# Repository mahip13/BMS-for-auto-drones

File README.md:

This directory contains schematics and simulationsfor the BMS for autonomous drones 

The .asc or SPICE file simulates all the respective parts of the circuit such as voltage sensing current sensing overcharge and overcurrent protection

Moreover the firmware (multichannel_adc file) is based on STM32F103 which includes multichannel ADC calculation for differnet sensors (3 temperature sensors, 4 current sensors, 1 voltage sensing circuit)

The real-time communication is still in process

This directory does not include the final PCB design

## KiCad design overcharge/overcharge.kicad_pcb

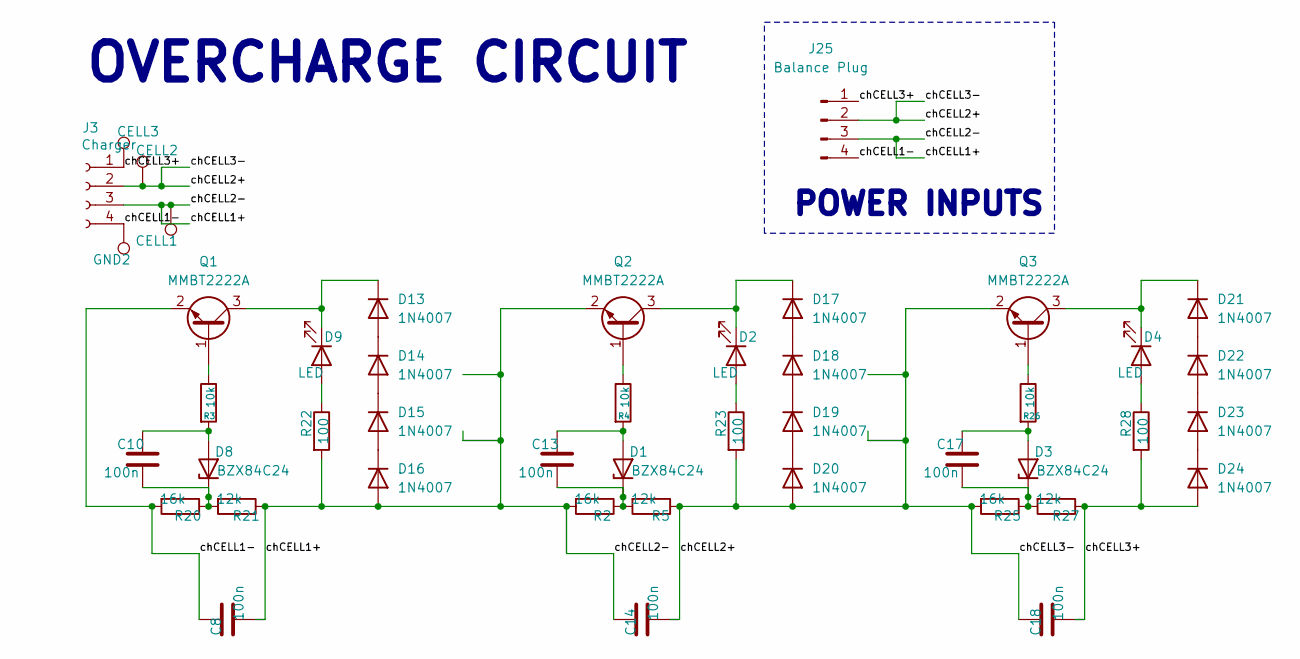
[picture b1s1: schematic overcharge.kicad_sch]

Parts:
C8: 100n; C_1206_3216Metric
C10, C13, C17: 100n; C_0805_2012Metric_Pad1.18x1.45mm_HandSolder
C14, C18: 100n; C_1206_3216Metric_Pad1.33x1.80mm_HandSolder
CELL1, CELL2, CELL3: TestPoint; Pin_D1.0mm_L10.0mm
D1, D3, D8: BZX84C24; SOT-23
D2, D4, D9: LED; LED_0805_2012Metric_Pad1.15x1.40mm_HandSolder
D13, D14, D15, D16, D17, D18, D19, D20, D21, D22, D23, D24: 1N4007; D_DO-41_SOD81_P10.16mm_Horizontal
GND2: TestPoint; Pin_D1.0mm_L10.0mm
J3: Charger; JST_XH_B4B-XH-A_1x04_P2.50mm_Vertical
J25: Balance Plug; JST_XH_S4B-XH-A_1x04_P2.50mm_Horizontal
Q1, Q2, Q3: MMBT2222A; SOT-23
R2, R20, R25: 16k; R_0603_1608Metric_Pad0.98x0.95mm_HandSolder
R3, R4, R26: 10k; R_0805_2012Metric_Pad1.20x1.40mm_HandSolder
R5, R21, R27: 12k; R_0603_1608Metric_Pad0.98x0.95mm_HandSolder
R22, R23, R28: 100; R_0603_1608Metric_Pad0.98x0.95mm_HandSolder

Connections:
/chCELL1+: C8.2, C14.1, CELL1.1, D16.2 (A), J3.3, J25.3, Q2.2 (E), R2.2, R21.1, R22.2
/chCELL1-: C8.1, GND2.1, J3.4, J25.4, Q1.2 (E), R20.2
/chCELL2+: C14.2, C18.1, CELL2.1, D20.2 (A), J3.2, J25.2, Q3.2 (E), R5.1, R23.2, R25.2
/chCELL3+: C18.2, CELL3.1, D24.2 (A), J3.1, J25.1, R27.1, R28.2
unnamed: C13.1, D1.1 (A), R4.2
unnamed: C13.2, D1.3 (K), R2.1, R5.2
unnamed: D2.2 (A), R23.1
unnamed: C17.1, D3.1 (A), R26.2
unnamed: C17.2, D3.3 (K), R25.1, R27.2
unnamed: D4.2 (A), R28.1
unnamed: C10.1, D8.1 (A), R3.2
unnamed: C10.2, D8.3 (K), R20.1, R21.2
unnamed: D9.2 (A), R22.1
unnamed: D13.2 (A), D14.1 (K)
unnamed: D9.1 (K), D13.1 (K), Q1.3 (C)
unnamed: D14.2 (A), D15.1 (K)
unnamed: D15.2 (A), D16.1 (K)
unnamed: D17.2 (A), D18.1 (K)
unnamed: D2.1 (K), D17.1 (K), Q2.3 (C)
unnamed: D18.2 (A), D19.1 (K)
unnamed: D19.2 (A), D20.1 (K)
unnamed: D21.2 (A), D22.1 (K)
unnamed: D4.1 (K), D21.1 (K), Q3.3 (C)
unnamed: D22.2 (A), D23.1 (K)
unnamed: D23.2 (A), D24.1 (K)
unnamed: Q1.1 (B), R3.1
unnamed: Q2.1 (B), R4.1
unnamed: Q3.1 (B), R26.1

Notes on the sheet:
POWER INPUTS
OVERCHARGE CIRCUIT

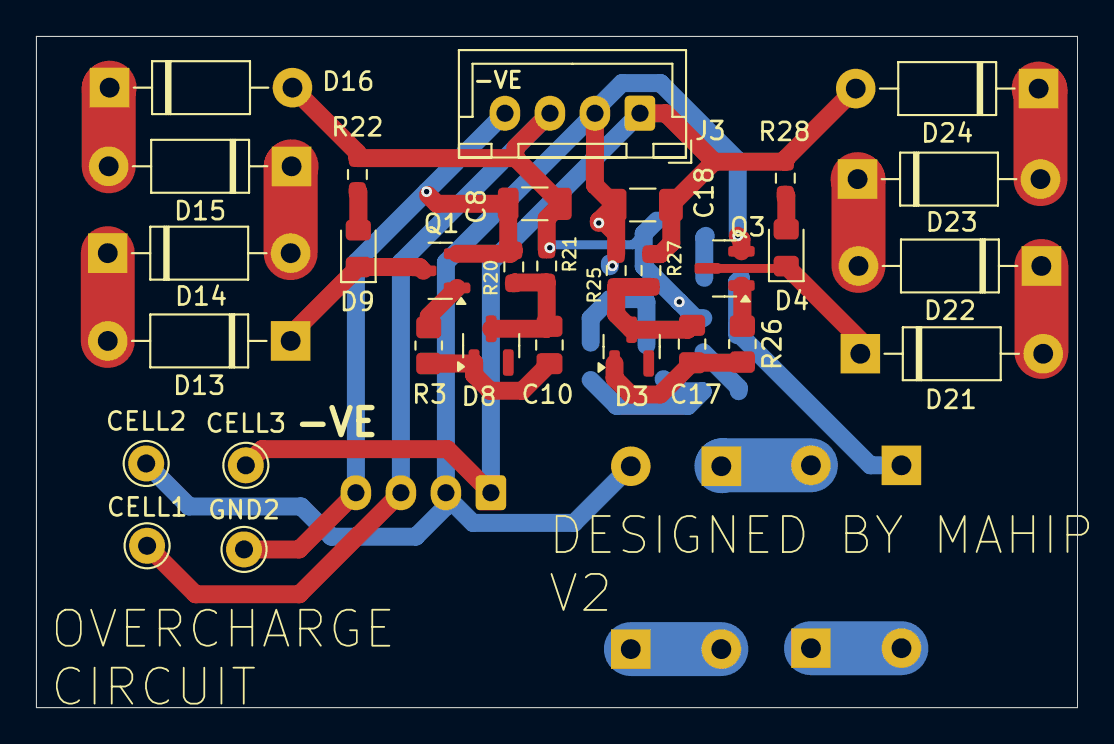
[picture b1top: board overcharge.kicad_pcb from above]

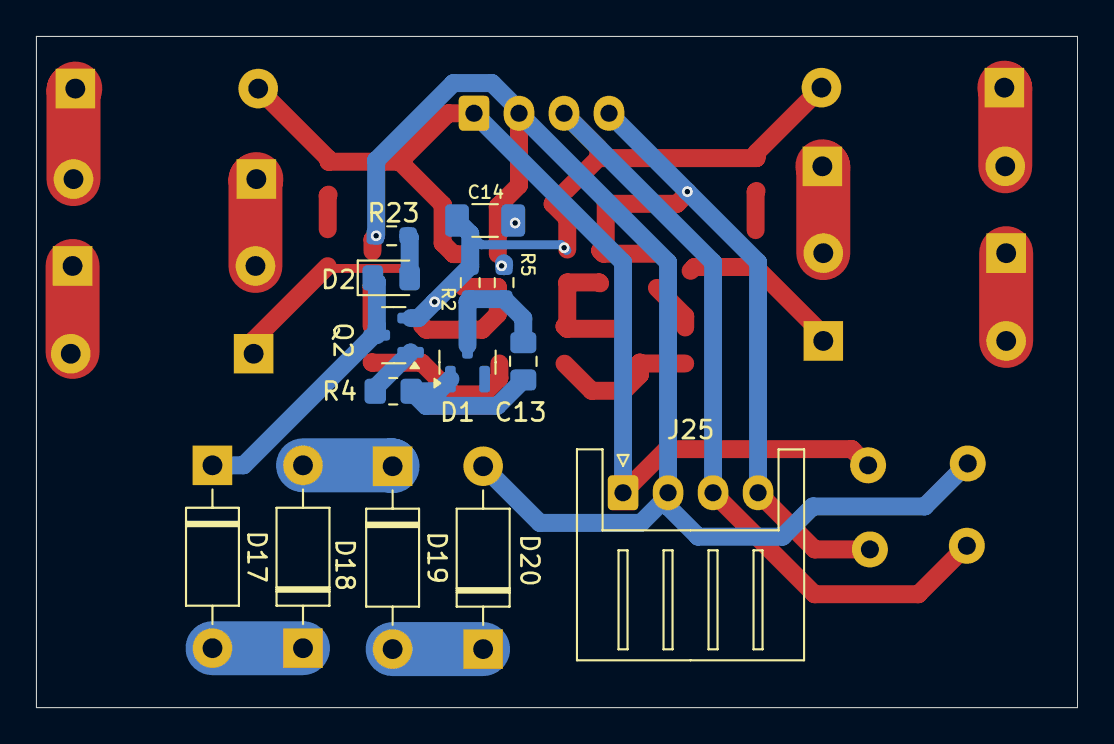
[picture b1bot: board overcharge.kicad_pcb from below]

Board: 2 copper layers, 57.8 x 37.3 mm, 45 parts (14 on the bottom side), 28 nets.

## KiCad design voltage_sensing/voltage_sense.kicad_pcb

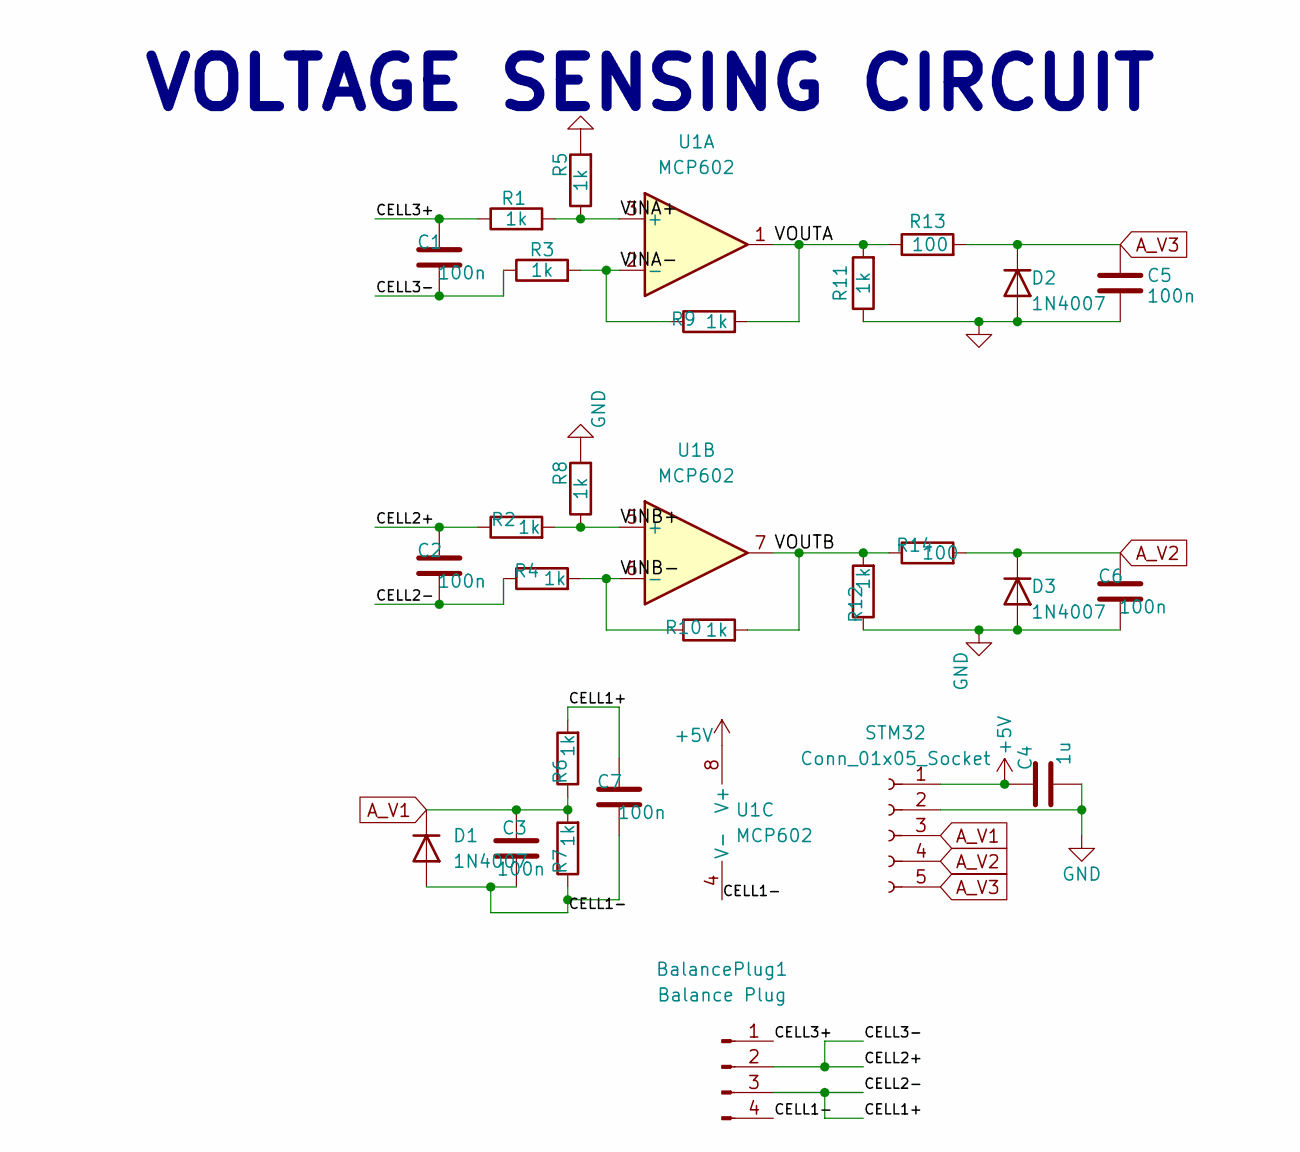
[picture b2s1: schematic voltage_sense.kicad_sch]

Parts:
BalancePlug1: Balance Plug; JST_XH_S4B-XH-A_1x04_P2.50mm_Horizontal
C1, C2, C3, C5, C6, C7: 100n; C_0805_2012Metric_Pad1.18x1.45mm_HandSolder
C4: 1u; C_0805_2012Metric_Pad1.18x1.45mm_HandSolder
D1, D2, D3: 1N4007; D_DO-41_SOD81_P10.16mm_Horizontal
R1, R2, R3, R4, R5, R6, R7, R8, R9, R10, R11, R12: 1k; R_0603_1608Metric_Pad0.98x0.95mm_HandSolder
R13, R14: 100; R_0603_1608Metric_Pad0.98x0.95mm_HandSolder
STM32: Conn_01x05_Socket; PinSocket_1x05_P2.54mm_Vertical
U1: MCP602; TDFN-8-1EP_3x2mm_P0.5mm_EP1.3x1.4mm

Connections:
+5V: C4.1, STM32.1, U1.8 (V+)
/CELL1+: BalancePlug1.3, C2.2, C7.1, R4.1, R6.2; also elsewhere on the board
/CELL1-: BalancePlug1.4, C3.2, C7.2, D1.2 (A), R7.1, U1.4 (V-); also elsewhere on the board
/CELL2+: BalancePlug1.2, C1.2, C2.1, R2.1, R3.1; also elsewhere on the board
/CELL3+: BalancePlug1.1, C1.1, R1.1; also elsewhere on the board
/VINA+: R1.2, R5.1, U1.3 (+)
/VINA-: R3.2, R9.1, U1.2 (-)
/VINB+: R2.2, R8.1, U1.5 (+)
/VINB-: R4.2, R10.1, U1.6 (-)
/VOUTA: R9.2, R11.2, R13.1, U1.1
/VOUTB: R10.2, R12.2, R14.1, U1.7
A_V1: C3.1, D1.1 (K), R6.1, R7.2, STM32.3
A_V2: C6.1, D3.1 (K), R14.2, STM32.4
A_V3: C5.1, D2.1 (K), R13.2, STM32.5
GND: C4.2, C5.2, C6.2, D2.2 (A), D3.2 (A), R5.2, R8.2, R11.1, R12.1, STM32.2

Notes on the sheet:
VOLTAGE SENSING CIRCUIT

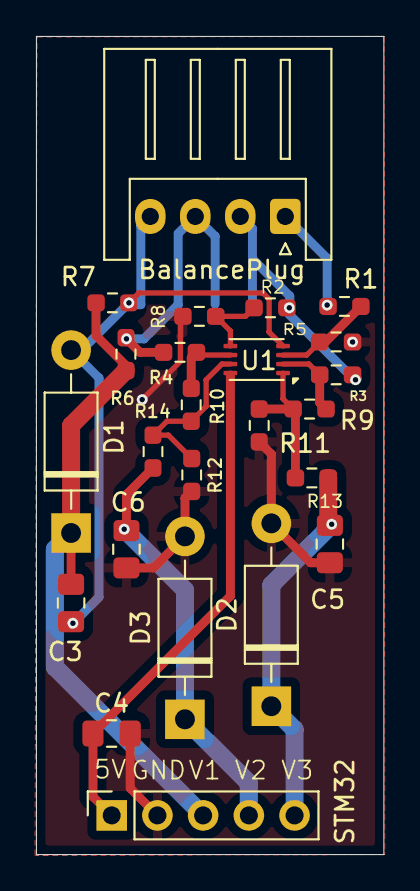
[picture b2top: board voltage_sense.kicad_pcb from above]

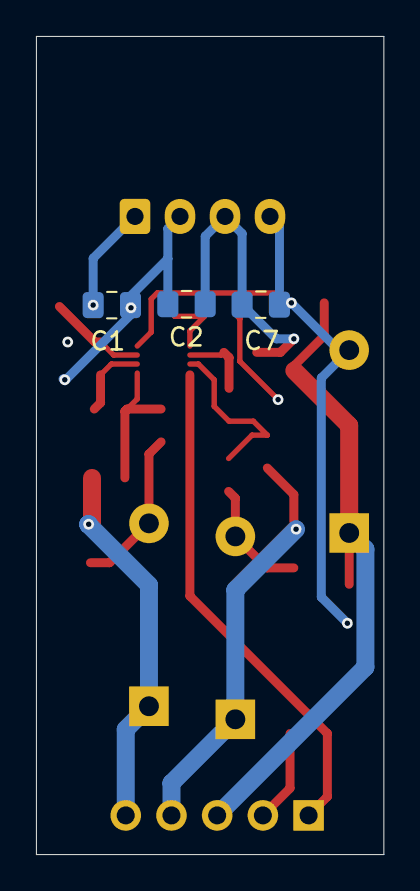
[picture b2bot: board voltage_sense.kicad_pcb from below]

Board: 2 copper layers, 19.3 x 45.5 mm, 27 parts (3 on the bottom side), 15 nets.

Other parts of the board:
BalancePlug: Balance Plug; JST_XH_S4B-XH-A_1x04_P2.50mm_Horizontal

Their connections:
/CELL1+: BalancePlug.3; also elsewhere on the board
/CELL1-: BalancePlug.4; also elsewhere on the board
/CELL2+: BalancePlug.2; also elsewhere on the board
/CELL3+: BalancePlug.1; also elsewhere on the board

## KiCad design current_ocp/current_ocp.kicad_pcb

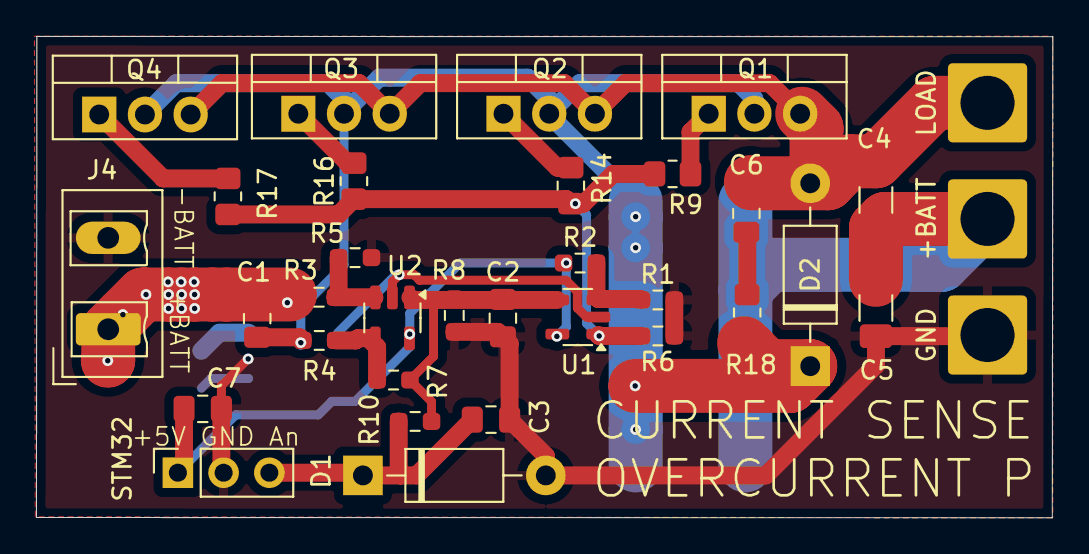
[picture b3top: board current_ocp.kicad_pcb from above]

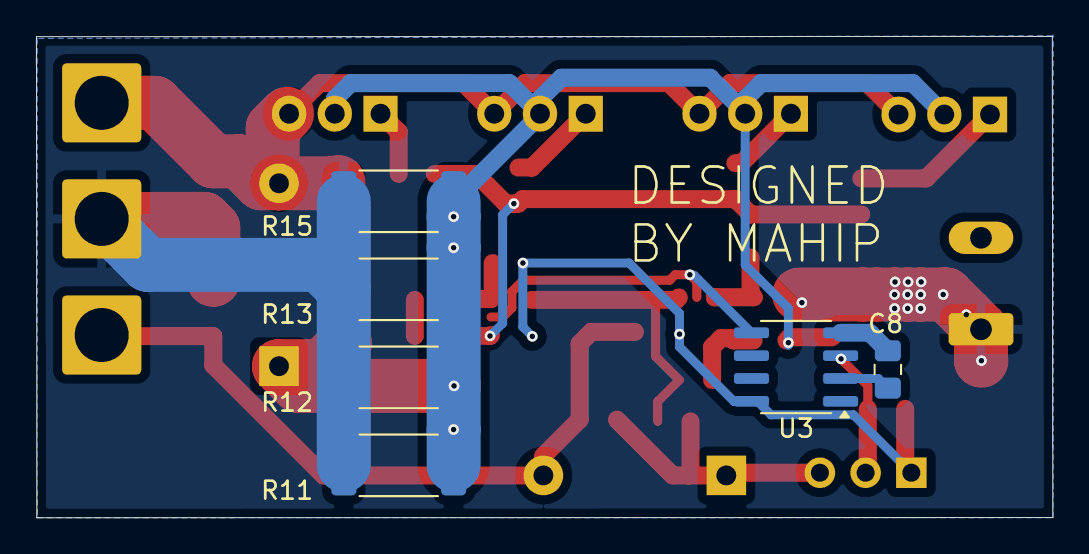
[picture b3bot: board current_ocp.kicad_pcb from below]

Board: 2 copper layers, 56.5 x 26.7 mm, 40 parts (6 on the bottom side), 19 nets.

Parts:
+BATT: Conn_01x01_Socket; SolderWire-2.5sqmm_1x01_D2.4mm_OD4.4mm
C1, C2, C3, C8: 100n; C_0805_2012Metric_Pad1.18x1.45mm_HandSolder
C4, C5: 10u; C_1206_3216Metric_Pad1.33x1.80mm_HandSolder
C6, C7: 1u; C_0805_2012Metric_Pad1.18x1.45mm_HandSolder
D1, D2: 1N4007; D_DO-41_SOD81_P10.16mm_Horizontal
GND: Conn_01x01_Socket; SolderWire-2.5sqmm_1x01_D2.4mm_OD4.4mm
J4: DischargePlug; PhoenixContact_MCV_1,5_2-G-5.08_1x02_P5.08mm_Vertical
LOAD: Conn_01x01_Socket; SolderWire-2.5sqmm_1x01_D2.4mm_OD4.4mm
Q1, Q2, Q3, Q4: IRLZ44N; TO-220-3_Vertical
R1: 7.5k; R_0603_1608Metric_Pad0.98x0.95mm_HandSolder
R2: 20k; R_0603_1608Metric_Pad0.98x0.95mm_HandSolder
R3, R4, R6, R8, R10: 1k; R_0603_1608Metric_Pad0.98x0.95mm_HandSolder
R5, R7: 10k; R_0603_1608Metric_Pad0.98x0.95mm_HandSolder
R9, R14, R16, R17: 10; R_0805_2012Metric_Pad1.20x1.40mm_HandSolder
R11, R13: 0.01; R_2512_6332Metric_Pad1.40x3.35mm_HandSolder
R12, R15: 0.1; R_2512_6332Metric_Pad1.40x3.35mm_HandSolder
R18: 100; R_0805_2012Metric_Pad1.20x1.40mm_HandSolder
STM32: STM32; PinSocket_1x03_P2.54mm_Vertical
U1, U2: OPA333xxDBV; SOT-23-5
U3: ICL7660; SOIC-8_3.9x4.9mm_P1.27mm

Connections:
+5V: C7.1, R2.1, STM32.1, U1.5 (V+), U2.5 (V+), U3.8 (V+)
+12.6V: +BATT.1, C1.1, C4.2, C5.1, J4.1, R3.1, R11.2, R12.2, R13.2, R15.2
-5_1V: U1.2 (V-), U2.2 (V-), U3.5 (VOUT)
/inv1: C2.1, R7.2, R8.2, R10.2, U1.4 (-), U2.1
/shunt1-: C1.2, D2.1 (K), Q1.2 (D), Q2.2 (D), Q3.2 (D), Q4.2 (D), R4.1, R11.1, R12.1, R13.1, R15.1, R18.1
A_i1: C3.1, D1.1 (K), R10.1, STM32.3
GND: C2.2, C3.2, C5.2, C7.2, D1.2 (A), GND.1, J4.2, R1.2, R5.2, R6.1, R8.1, STM32.2, U3.3 (GND)
unnamed: C6.1, R18.2
unnamed: C4.1, C6.2, D2.2 (A), LOAD.1, Q1.3 (S), Q2.3 (S), Q3.3 (S), Q4.3 (S)
unnamed: Q1.1 (G), R9.2
unnamed: Q2.1 (G), R14.2
unnamed: Q3.1 (G), R16.2
unnamed: Q4.1 (G), R17.2
unnamed: R6.2, R9.1, R14.1, R16.1, R17.1, U1.1
unnamed: R1.1, R2.2, U1.3 (+)
unnamed: R3.2, R5.1, U2.3 (+)
unnamed: R4.2, R7.1, U2.4 (-)
unnamed: C8.1, U3.2 (CAP+)
unnamed: C8.2, U3.4 (CAP-)
